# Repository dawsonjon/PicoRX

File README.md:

Pi Pico Rx Transceiver Experiments
----------------------------------

This branch contains an experimental build investigating the addition of
transmit capability to the Pi Pico RX receiver platform.

Some time ago I developed a standalone transmitter based on similar techniques
and hardware. While it appeared feasible to combine this transmitter with the
Pi Pico RX to create a simple transceiver, the resulting spurious performance
was not satisfactory. Although the concept worked, unwanted emissions and
spectral purity became significant concerns that needed to be addressed before
the approach could be considered practical.

The primary goal of these experiments is therefore to investigate methods of
improving spurious performance and to assess the overall viability of building
a simple, low-cost transceiver around the Pi Pico RX architecture.

A number of different approaches have been explored. Some experiments focus on
incremental improvements to the original design, while others revisit the
problem from first principles and investigate entirely different transmitter
architectures. Along the way I have also examined a range of more advanced
transmit features, including speech processing and Controlled Envelope Single
Sideband (CESSB), to better understand what level of performance can
realistically be achieved using the RP2040/RP2350 platform.

The results presented here are not intended as a finished design. Rather, they
document an ongoing engineering investigation into the capabilities and
limitations of software-defined transmit techniques on the Raspberry Pi Pico,
highlighting both successful approaches and ideas that proved less
effective than expected.

Caution
=======

This branch is an experimental research effort and should be viewed in the
spirit of scientific exploration rather than as a finished design.

The material presented here documents investigations, prototypes, measurements,
successes, and failures as I explore the possibility of adding transmit
capability to the Pi Pico RX platform. Many of the techniques and circuits
described are works in progress and may change substantially as the project
evolves.

No guarantees are made regarding performance, spectral purity, regulatory
compliance, or suitability for on-air operation. In particular, some
experimental transmitter configurations may produce unacceptable levels of
spurious emissions or other unwanted signals. Anyone wishing to reproduce
these experiments is responsible for verifying the performance of their own
equipment and ensuring compliance with applicable regulations before
transmitting.

This project should not be considered a construction guide, product, or
recommendation for practical use. Designs, software, hardware configurations,
and conclusions may change significantly as new ideas are tested and better
approaches are discovered.

Finally, while I am happy to share my findings, I am unable to provide ongoing
support for individual builds, hardware modifications, bug fixes,
troubleshooting, or feature requests. The information is published primarily as
a record of my own experiments and to encourage further investigation by
others with similar interests.

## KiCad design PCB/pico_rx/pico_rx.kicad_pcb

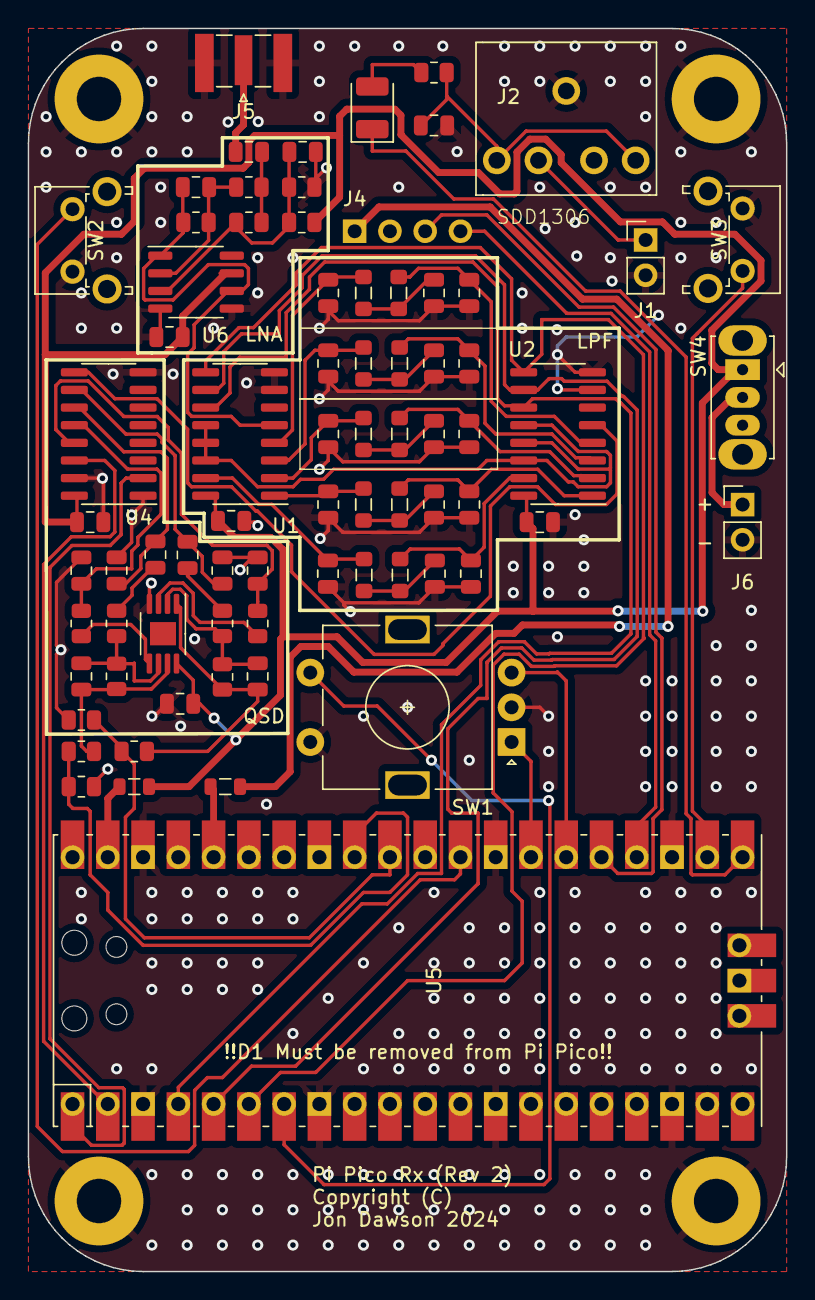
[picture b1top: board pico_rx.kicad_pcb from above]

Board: 2 copper layers, 54.6 x 89.5 mm, 80 parts (0 on the bottom side), 58 nets.

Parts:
C1: 10n; C_0805_2012Metric
C2, C3, C10, C17, C24, C25: 100n; C_0805_2012Metric
C4, C11: 10u; C_0805_2012Metric
C5: 22p; C_0805_2012Metric
C6, C9: 680p; C_0805_2012Metric
C7, C13, C14, C15: 1n; C_0805_2012Metric
C8: 330pF; C_0805_2012Metric
C12: 470p; C_0805_2012Metric
C16: 330p; C_0805_2012Metric
C19, C22: 1.5n; C_0805_2012Metric
C21: 2.2n; C_0805_2012Metric
C26, C27, C28, C29: 15n; C_0805_2012Metric
C30, C31: 27p; C_0805_2012Metric
C34: 470n; C_0805_2012Metric
C36, C38: 3.3n; C_0805_2012Metric
C37: 4.7n; C_0805_2012Metric
C39: 100u; CP_EIA-3528-21_Kemet-B
FB1, FB2: Ferrite_Bead; L_0805_2012Metric
H1, H2, H3, H4: MountingHole_Pad; MountingHole_3.2mm_M3_Pad
J1: Speaker; PinHeader_1x02_P2.54mm_Vertical
J2: Headphone; jack3.5mm switched
J4: I2C Display; SDD1306
J5: Antenna; SMA_Samtec_SMA-J-P-X-ST-EM1_EdgeMount
J6: Battery; PinHeader_1x02_P2.54mm_Vertical
L1, L2: 330n; L_0805_2012Metric_Pad1.05x1.20mm_HandSolder
L3, L4: 1u; L_0805_2012Metric_Pad1.05x1.20mm_HandSolder
L5, L13: 220n; L_0805_2012Metric_Pad1.05x1.20mm_HandSolder
L6, L7: 2.2u; L_0805_2012Metric_Pad1.05x1.20mm_HandSolder
L8, L9: 4.7u; L_0805_2012Metric_Pad1.05x1.20mm_HandSolder
R1: 47; R_0805_2012Metric
R2, R10: 10K; R_0805_2012Metric
R3, R4, R5, R6, R9: 100; R_0805_2012Metric
R7, R8: 100k; R_0805_2012Metric
R11: 220; R_0805_2012Metric
R12, R15, R16: 1k; R_0805_2012Metric
R13, R14: 470; R_0805_2012Metric
SW1: RotaryEncoder_Switch; RotaryEncoder_Alps_EC11E-Switch_Vertical_H20mm
SW2, SW3: SW_Push; SW_Tactile_SPST_Angled_PTS645Vx31-2LFS
SW4: SW_SPDT; SW_Slide_1P2T_CK_OS102011MS2Q
U1, U2: 74CBT3251; SOIC-16_3.9x9.9mm_P1.27mm
U3: LTC6227; MSOP-8-1EP_3x3mm_P0.65mm_EP1.68x1.88mm
U4: FST3253; SOIC-16_3.9x9.9mm_P1.27mm
U5: Pico; RPi_Pico_SMD_TH
U6: LTC6226xS8; SO-8_3.9x4.9mm_P1.27mm

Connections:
+3V3: FB1.2, J4.1
+5V: C2.1, C3.1, C10.1, C24.1, C25.1, FB2.2, R2.1, SW4.1 (A), U1.16 (VCC), U2.16 (VCC), U3.8 (V+), U4.16 (VCC), U6.7 (V+)
/PI Pico/BUTTON_BACK: SW3.2, U5.22 (GPIO17)
/PI Pico/BUTTON_FWD: SW2.2, U5.29 (GPIO22)
/PI Pico/ENCODER_A: SW1.A, U5.27 (GPIO21)
/PI Pico/ENCODER_B: SW1.B, U5.26 (GPIO20)
/PI Pico/PUSH: SW1.S1, U5.7 (GPIO5)
/PI Pico/SCL: J4.3, U5.25 (GPIO19)
/PI Pico/SDA: J4.4, U5.24 (GPIO18)
BAND_0: U1.11 (S0), U2.11 (S0), U5.4 (GPIO2)
BAND_1: U1.10 (S1), U2.10 (S1), U5.5 (GPIO3)
BAND_2: U1.9 (S2), U2.9 (S2), U5.6 (GPIO4)
GND: C2.2, C3.2, C6.1, C7.1, C8.1, C9.1, C10.2, C12.1, C13.1, C14.1, C15.1, C16.1, C17.2, C19.1, C21.1, C22.1, C24.2, C25.2, C26.1, C27.1, C28.1, C29.1, C34.2, C36.1, C37.1, C38.1, H1.1, H2.1, H3.1, H4.1, J1.2, J2.G, J4.2, J5.2 (Ext), J6.2, R10.2, R15.1, R16.1, SW1.C, SW1.S2, SW2.1, SW3.1, U1.7 (~OE), U1.8 (GND), U2.7 (~OE), U2.8 (GND), U3.4 (V-), U4.1 (1~OE), U4.8 (GND), U4.15 (2~OE), U5.3 (GND), U5.8 (GND), U5.13 (GND), U5.18 (GND), U5.23 (GND), U5.28 (GND), U5.38 (GND), U6.4 (V-), U6.5 (V-)
LO_I: U4.14 (S0), U5.2 (GPIO1)
LO_Q: U4.2 (S1), U5.1 (GPIO0)
LPF_1_2_A: C36.2, L8.2, U1.15 (I4)
LPF_1_2_B: C38.2, L9.1, U2.15 (I4)
LPF_2_4_A: C19.2, L6.2, U1.1 (I3)
LPF_2_4_B: C22.2, L7.1, U2.1 (I3)
LPF_4_8_A: C13.2, L3.2, U1.2 (I2)
LPF_4_8_B: C15.2, L4.1, U2.2 (I2)
LPF_8_16_A: C6.2, L1.2, U1.3 (I1)
LPF_8_16_B: C9.2, L2.1, U2.3 (I1)
LPF_16_30_A: C8.2, L13.2, U1.4 (I0)
LPF_16_30_B: C16.2, L5.1, U2.4 (I0)
unnamed: C1.1, R1.1, R12.2
unnamed: C4.1, R3.2
unnamed: C7.2, L1.1, L2.2
unnamed: C11.1, R5.2
unnamed: C12.2, L5.2, L13.1
unnamed: C14.2, L3.1, L4.2
unnamed: C21.2, L6.1, L7.2
unnamed: C34.1, J2.S, J2.T, R9.2
unnamed: C37.2, L8.1, L9.2
unnamed: C39.2, R9.1
unnamed: J1.1, J2.TN
unnamed: C1.2, J5.1 (In)
unnamed: J6.1, SW4.2 (B)
unnamed: U1.12 (I7), U1.13 (I6), U1.14 (I5), U2.12 (I7), U2.13 (I6), U2.14 (I5)
unnamed: R6.1, U3.3 (+)
unnamed: C31.1, R5.1, R8.1, U3.2 (-)
unnamed: R4.1, U3.5 (+)
unnamed: C30.1, R3.1, R7.1, U3.6 (-)
unnamed: C11.2, C27.2, U4.10 (2B1)
unnamed: C4.2, C26.2, U4.11 (2B2)
unnamed: C28.2, R4.2, U4.12 (2B3)
unnamed: C29.2, R6.2, U4.13 (2B4)
unnamed: FB1.1, U5.36 (3V3)
unnamed: R14.1, R15.2, U5.31 (GPIO26_ADC0)
unnamed: R13.1, R16.2, U5.32 (GPIO27_ADC1)
unnamed: FB2.1, U5.39 (VSYS)
unnamed: C17.1, R2.2, R10.1, R12.1, U6.3 (+)
unnamed: C5.1, R1.2, R11.1, U6.2 (-)
RF_BPF: U2.5 (Y), U4.9 (2A)
RF_PREAMP: C5.2, R11.2, U1.5 (Y), U6.1 (FB), U6.6
RX_I: C30.2, R7.2, R13.2, U3.7
RX_Q: C31.2, R8.2, R14.2, U3.1
SPEAKER: C39.1, U5.21 (GPIO16)

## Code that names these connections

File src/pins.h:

#ifndef __PINS__
#define __PINS__

// GPIO        0  1  2  3  4  5  6  7  8  9  10 11 12 13 14 15
// PWM Channel 0A 0B 1A 1B 2A 2B 3A 3B 4A 4B 5A 5B 6A 6B 7A 7B
//
// GPIO        16 17 18 19 20 21 22 23 24 25 26 27 28 29
// PWM Channel 0A 0B 1A 1B 2A 2B 3A 3B 4A 4B 5A 5B 6A 6B

const uint8_t PIN_NCO_1 = 0;
const uint8_t PIN_NCO_2 = 1;
const uint8_t PIN_BAND_0 = 2;
const uint8_t PIN_BAND_1 = 3;
const uint8_t PIN_BAND_2 = 4;
const uint8_t PIN_ENCODER_PUSH = 5;
const uint8_t PIN_PTT = 6;
const uint8_t PIN_DIT = 7;
const uint8_t PIN_MISO = 8;
const uint8_t PIN_DAH = 9;
const uint8_t PIN_MAGNITUDE = 10; // shared pin, changes use in polar/rectangular mode
const uint8_t PIN_TX_I = 10;      // PWM channel 5A
const uint8_t PIN_DC = 11;
const uint8_t PIN_RF = 12;   // must be HSTX capable
const uint8_t PIN_TX_Q = 12; // PWM channel 6A
const uint8_t PIN_CS = 13;
const uint8_t PIN_SCK = 14;
const uint8_t PIN_MOSI = 15;
const uint8_t PIN_AUDIO = 16; // PWM channel 0A
const uint8_t PIN_BACK = 17;
const uint8_t PIN_DISPLAY_SDA = 18;
const uint8_t PIN_DISPLAY_SCL = 19;
const uint8_t PIN_AB = 20;
const uint8_t PIN_B = 21;
const uint8_t PIN_MENU = 22;
const uint8_t PIN_PSU = 23;
const uint8_t PIN_VBUS_SENSE = 24;
const uint8_t LED = 25;
const uint8_t PIN_ADC_I = 26;
const uint8_t PIN_ADC_Q = 27;
const uint8_t PIN_MIC = 28;
const uint8_t PIN_BATTERY = 29;

#endif

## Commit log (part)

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2024-09-13 Added waterfall page
2024-09-13 Added ticks to waterfall
2024-09-13 Completed display scrolling ssd1306_scroll_screen(&disp, x, y ); - Scrolling in all 4 directions works
2024-09-13 Add simple scheduler and state machines
2024-09-14 Added signal strength to Recall page - left some commented out style options in for now
    factred out int ui::dBm_to_S(float power_dBm);
2024-09-14 Reworked recall signal strength to be vertical bar
2024-09-14 top level menu no longer quits to home after an action - except Recall - you're probably done with the menus then...
2024-09-14 and config menu doesnt go back home
2024-09-14 Make waterfall look nice
2024-09-15 Added symbols the the font: speaker, play, reverse play, record, stop, pause
2024-09-15 created memory_scan and put memory_recall back to the way it was
    UI fiddling in memory_scan
    ssd1306_draw_char only clears background for colour 0 and 1
2024-09-15 Typo fix
2024-09-15 fix for Menu up no longer goes home - the changes never made it to the radio side
2024-09-15 Just a minor adjustment
2024-09-15 Use nicer fonts
2024-09-15 Add nicer font
2024-09-16 display_draw_str and char again support arbitrary scaling of fonts. - if odd, scale the 8x6; if even scale the 16x12 - fixes my splash screen :)
    ssd1306_draw_char_with_font()
    fix logic on preclearing background of character cell.
    - if drawing black, clear with white
    - if drawing white, clear with black
    - if colour==2, do nothing so OR/XOR drawing works
2024-09-16 Small adjustment
2024-09-16 fic draw_h_tick_marks() wrong Y offset on a couple of the ticks
2024-09-16 WIP "analog" S meter
2024-09-16 Use power_dBm for better resolution
2024-09-16 Sync the mode values with firmware
2024-09-17 finished move gauge render to separate function
2024-09-17 ticks can be labelled
    renamed some variables
    fixed off by 1 on tick count
    fixed init of dBm averages to be -FLT_MAX
2024-09-17 Add slow ramping of audio to prevent clicks and pops on power up and during frequency change
2024-09-17 Add signal strength meter back into recall menu
2024-09-17 Fix freeze when attempting to store
2024-09-18 Analog meter returns if you ask for height zero (rather than crash with DIV0)
    Analog meter can draw a rectangular style with a negative height.
2024-09-18 memory_scan() speed display uses new double height font
    display_print_char() can print in style_xor
2024-09-18 frequency_scan() speed display uses new double height font
    factored out display_print_speed(int16_t x, int16_t y, uint32_t scale, int speed);
    display_print_speed now supports scale
2024-09-19 Tweaked 16x12 speaker icon
2024-09-19 Added audio de-emphasis
2024-09-19 Add cat capability
2024-09-19 tidy up cat control
2024-09-19 Added 9kHz steps - good for MW broadcast in some territories
2024-09-19 Fixed typo
2024-09-19 Fixed periodic audio cut out
2024-09-20 fix subtle bug where on exiting display_timeout, you'd get dropped into another hw_config menu based on the selected timeout :)
    oled contrast is now stored in bits of hw_setup
    s/enum_deemphasis/flag_deemphasis
    added mask_deemphasis
2024-09-20 Improve robustness of CAT interface
2024-09-20 Add configuration for TFT
2024-09-21 Expose squelch state so the scanner can use it
2024-09-21 Update display to show listen vs scanning
2024-09-21 Added scanner_radio_menu() with a subset of the main menu for quicker access in the scanner
    any press on back -> quit and restore radio settings
    short press on "menu" -> launches scanner_radio_menu()
    long press on menu -> select station and quit
2024-09-21 Show squelch level in vertical signal strength
2024-09-21 Add frequency calibration
2024-09-21 tweak scanning
2024-09-24 ported the frequency_scan() code to memory_scan()
2024-09-25 Can now set encoder resolution. Suits encoders with twice as many pulses per indent
2024-09-25 Integrated the encoder handling with the other events
2024-09-25 Make sure display is refreshed as fast as possible
2024-09-29 Added Bresenham audio interpolation
2024-09-29 Block display updated if screen is "shutdown"
2024-09-30 USB audio streaming adjustments
2024-10-01 USB Volume is fixed at volume level 8
2024-10-01 Reverted relabeling to avoid Linquistic warfare
    USB audio is grabbed after the AGC with no scaling
2024-10-01 Added volume level and USB icon to main page
2024-10-01 Make volume controllable via encoder
2024-10-02 WIP: spectrum zoom
2024-10-02 Also apply spectrum zoom to waterfall
2024-10-02 Spectrum zoom settings are saved
2024-10-02 Add CDC USB descriptors and enable usb stdio
2024-10-02 Fixed one event type
2024-10-03 exposed usb volume and mute controls with callbacks
2024-10-03 Fix scanner button logic to a) work again and b) benefit from the short/long logic rather than my own
2024-10-03 added critical_section wrappers in an abundance of caution
2024-10-03 Moved USB streaming to core0 to offload core1 a bit
2024-10-03 Added u8g2 and merged it with current display driver
2024-10-03 Fixed scrolling
2024-10-04 M_PI to keep vscode from flagging problems
    fix splash screen button/encoder handling
    move some code out of button_state computation
    - I want to separate out the button_state computation for use elsewhere
    - moved any code that doesn't contribute to this
2024-10-04 Changed scanner buttons Back short click => exit rollback settings Back long press => exit keep current settings Menu short click => Radio options Menu long click => does nothing now
2024-10-04 Added the code needed to record and decode a screen dump
2024-10-04 Leave only digits in the fonts
2024-10-04 Changed fonts to non-italic
2024-10-04 submodules - add u9g2 - remove pico-ssd1306 (but not "our" used files)
2024-10-04 Update build doco to setup submodules
2024-10-08 Switched to fixed 15k samplerate
2024-10-08 Adjust AGC speed together with mode
2024-10-08 Encoder change event latency reduction
2024-10-08 Improve the accuracy of button events decoding
2024-10-09 Added u8g2 to github actions and a small CMake cleanup
2024-10-09 Added missing dependencies and files
2024-10-10 various tweaks and bugfixes
2024-10-13 General tweak after merging
2024-10-17 Play around with IQ imbalance correction, and add some CPU optimisations
2024-10-17 Fix 9kHz step size issue
2024-10-19 Added more sophisticated squelch implementation
2024-10-19 Make the naming less ambiguous
2024-10-19 Added squelch timeout setting
2024-10-25 Add RGB/BGR colour options for TFT displays
2024-10-27 Add manual gain control, apply settings while changing menu options, save frequency immediately
2024-10-29 Use a bip buffer instead of a ring buffer
2024-10-30 Added optional CMSIS-based FFT filter implementation
2024-11-04 Update User Manual
2024-11-10 Various bug-fixes and tweaks
2024-11-12 Update manual
2024-11-21 Add unused submodule
2024-11-26 Add squelch timeout
2024-12-08 First attempt at noise reduction
2024-12-29 clean up cat interface
2025-01-05 Add experimental transmit capability
2025-01-05 Move pin definitions to a seperate file
2025-01-05 Make sure rf and magnitude pin are driven low when not transmitting
2025-01-11 Add refinements to PWM generation and add iambic CW keyer
2025-01-11 Add comment to pins
2025-01-26 Add improve performance of TX code
2025-01-26 Replace settings with a struct
2025-01-27 Get load working with new settings struct
2025-01-27 Get memory uploading to work
2025-03-02 Try to improve waterfall refresh rate
2025-03-09 Update error in user manual
2025-03-23 Add quadrature si5351 dependency
2025-03-24 Add nicer s-meter
2025-03-25 Add support for si/ms 5351 external NCO
2025-03-28 first cut at centralising hardware definitions.
2025-03-30 First cut at adding SSTV decoder
2025-04-01 Make SSTV mode switcheable
2025-04-04 Add frequency measurement
2025-04-05 Remove reset from waterfall
2025-04-25 Small cleanup
2025-04-25 Added unique serial to USB descriptors
2025-04-26 Adjust the IQ data layout
2025-04-26 Added USB streaming mode switch
2025-05-02 Added simple /noise canceler/spectral subtraction/
2025-05-03 Small adjustments to the noise canceler
2025-05-03 Fixed USB volume setting
2025-05-04 Further adjustments after testing
2025-05-04 Fixed "UI feedback" problem when setting encoder resolution
2025-05-04 Two small adjustments to the memory upload script
2025-05-05 Added missing files
2025-05-05 Refactored (separated) the encoder
2025-05-08 General refactor
2025-05-09 Added CORDIC-based magnitude estimator
2025-05-10 Two minor adjustments
2025-05-16 Added basic bass and treble control
2025-05-18 Added button encoder
2025-05-18 Fixed an error in some compilers
2025-05-18 Improved PLL in the synchronous AM demodulator
2025-05-18 Further optimization of magnitude calculations
2025-05-18 Switched to CORDIC-only phase and magnitude calculation
2025-05-19 Fixed phase wrapping (needs to be from -pi to +pi)
2025-05-19 Added simple polyphase PWM interpolator
2025-05-19 Move the busy time measurement past the PWM interpolation and syncing
2025-05-20 Small adjustments and fixes
2025-05-20 switch to using cat to upload memories
2025-05-20 Update frequency when PPM changes too
2025-05-21 Fixed the busy time measurement
2025-05-22 Added 3rd-order PLL in synchronous AM demodulator
2025-05-24 Adjusted the peak bin index
2025-05-24 Eliminated some magic numbers
2025-05-24 retune when if mode or frequency changes
2025-05-29 General convenience adjustments + some IIR decimator evaluation code
2025-05-29 Further adjustments and more plots
2025-05-29 Remove old comment
2025-05-31 IIR taps adjustments and commutator phase adjustment
2025-05-31 Added filter with even better response in ROI
2025-06-01 Use restructured text to generate manual for ease of maintenence
2025-06-02 Get SSTV decoder working
2025-06-04 Increase Pico1 clock speed to 150-200MHz
2025-06-04 Default OLED contrast fix
2025-06-12 Added GRC files which can be used in the "Raw IQ" USB streaming mode
2025-07-03 fix freq cal issue
2025-07-20 Add noise reduction animation and update concept schematic
2025-09-07 Window formula fix
2025-09-10 Removed duplicated code
2025-09-13 Refactor frequency switching
2025-09-13 Improvement on audio clicking during frequency tuning
2025-09-14 Added synchronous demodulator state resetting
2025-09-14 play around with click reduction mechanisms
2025-09-14 Assigned pinout for gorriatoqrp
2025-09-18 Fixed some unwanted commits
    Oooops
2025-09-19 Started TX implementation
    Very messy, but its the start :)
2025-09-19 Integrated W9RAN branch
    W9RAN branch of picorx had some good improvements for TX. It is now ported to the new version of PicoRX(Menus adapted), currently pwm audio doesnt work when keying the paddles WIP. Also still narrowi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
2025-09-26 Add zipped up binaries for convenience
2025-09-26 Added another display page - audio oscilloscope
2025-09-26 Added slim status to the oscilloscope page
2025-09-27 Let the SDK fetch the picotool
2025-09-27 Fix typo
2025-09-28 Added spectrum hold option
2025-10-03 VSCode code formatting
2025-10-10 Fix band switching
2025-10-12 Added GNURadio flowgraph for DRM recording
2025-10-18 Make the waterfall a little bit more informative by subtracting rough
    noise floor estimate
2025-11-23 NN denoiser:
    - network retrain with final hard sigmoid activation
    - configurable gain threshold
2025-11-24 Import transmit code
2025-11-24 Menu tweaks
2025-12-01 Add two tone test
2026-02-13 Use closest possible PLL frequency when transmitting
2026-02-14 Add ability to set frequency limits for transmit
2026-02-14 Add TX Audio Monitor
2026-02-19 Take account of clock doubling in best tx
2026-02-19 Scale waveform dither by phase increment
2026-02-21 First attempt to add IQ modulation
2026-02-24 Tidy up tuning, merge si5351 based polar transmitter
2026-02-27 Transmit basically working with all combinations of polar/iq, internal/external IQ
2026-02-28 Start drawing xcvr concept schemetic
2026-03-01 Refactor common transmit code
2026-03-01 Add DC bias compensation
2026-03-03 First pass speech processing
2026-03-08 Work reducing clicking
2026-03-13 Cleanup TX code
2026-05-06 Add latest binaries

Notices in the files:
PCB/pico_rx/pico_rx.kicad_pcb:
Copyright (C)
